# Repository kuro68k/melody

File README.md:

# melody
Melody generator for XMEGA. MIDI convert for desktop included.

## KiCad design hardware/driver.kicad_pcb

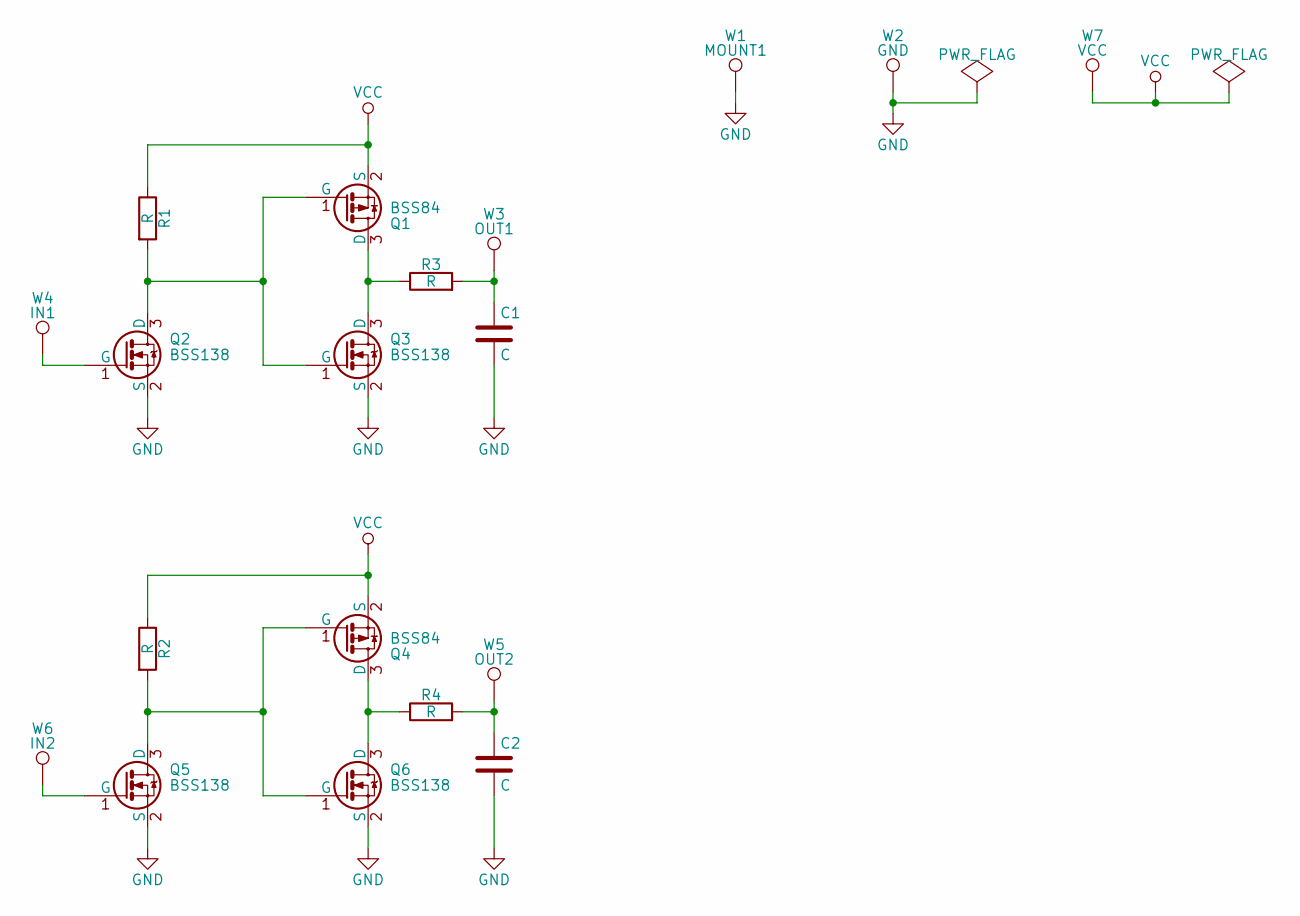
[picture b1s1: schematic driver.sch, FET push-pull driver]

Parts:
C1, C2: C; C_0603_HandSoldering
Q1, Q4: BSS84; SOT-23
Q2, Q3, Q5, Q6: BSS138; SOT-23
R1, R2, R3, R4: R; R_0603_HandSoldering
W1: MOUNT1; MountingHole_2.5mm_Pad
W2: GND; Measurement_Point_Square-TH_Big
W3: OUT1; Measurement_Point_Square-TH_Big
W4: IN1; Measurement_Point_Square-TH_Big
W5: OUT2; Measurement_Point_Square-TH_Big
W6: IN2; Measurement_Point_Square-TH_Big
W7: VCC; Measurement_Point_Square-TH_Big

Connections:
GND: C1.2, C2.2, Q2.2 (S), Q3.2 (S), Q5.2 (S), Q6.2 (S), W1.1, W2.1
unnamed: C1.1, R3.2, W3.1
unnamed: C2.1, R4.2, W5.1
unnamed: Q1.1 (G), Q2.3 (D), Q3.1 (G), R1.2
unnamed: Q1.3 (D), Q3.3 (D), R3.1
unnamed: Q2.1 (G), W4.1
unnamed: Q4.1 (G), Q5.3 (D), Q6.1 (G), R2.2
unnamed: Q4.3 (D), Q6.3 (D), R4.1
unnamed: Q5.1 (G), W6.1
VCC: Q1.2 (S), Q4.2 (S), R1.1, R2.1, W7.1

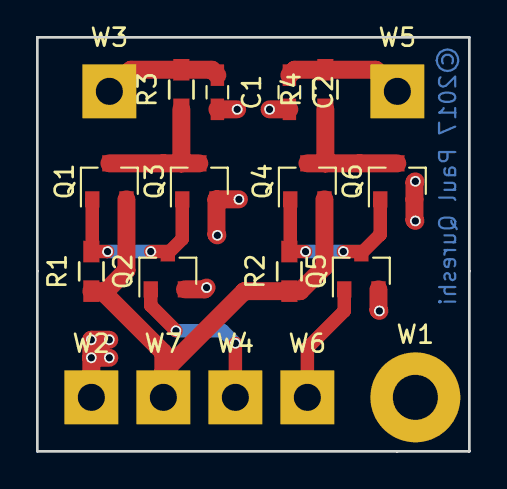
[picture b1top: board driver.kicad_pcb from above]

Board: 2 copper layers, 24.0 x 23.0 mm, 19 parts (0 on the bottom side), 10 nets.

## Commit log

2016-11-30 :confetti_ball: Added .gitattributes
2016-12-01 Added clock setup for test hardware platform
2016-12-28 Test sine wave working
2016-12-29 On-the-fly buffers working
2016-12-29 Sine wave from flash
2017-01-02 Removed some debug code
2017-01-08 Switched to test sine wave again
2017-01-08 Switched to PWM mode
2017-01-08 Fixed CPU clock
2017-01-08 128MHz PLL
2017-01-08 Enabled hi-res extension for 500KHz PWM
2017-01-08 Sine wave audible
2017-01-08 9 bit DAC
2017-01-08 PWM sample working
2017-01-08 Plays a little tune!
2017-01-13 Added control code support to midi-decode
2017-01-14 Added kamata4 tune
2017-01-15 Playback working
2017-01-15 Optimization attempt
2017-01-30 Added speaker driver schematicf
2017-02-01 Fixed FET orientation
2017-02-01 Added power flags
2017-02-01 Names/annotation
2017-02-01 Assigned footprints
2017-02-01 Initial PCB layout
2017-02-01 Routing
2017-02-02 Added optional RC filter
2017-02-03 Added logo
2017-02-03 Top silk
2017-02-03 Outlines on top silk
2017-02-05 Annotation completed
2017-02-05 PCB page notes
2017-02-05 Added licence info
2017-02-05 DRC, output
2017-02-05 Excluded V1.0 files from git
2017-02-20 Reduced mixing loop from ~750us to ~220us
2017-02-26 Test for mixer code with WAV output
2017-02-26 PWM fixed, sounds good
2017-03-11 per channel decay control for better note release
2017-07-23 debug output decoder
2017-07-23 debug output
2017-07-23 removed VS readme.txt
2017-07-23 Updated to match firmware
2017-07-23 removed debug, used stdio_fast instead
2017-07-23 Fixed decay LUT off by one error

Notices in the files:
hardware/driver.kicad_pcb:
CC BY-SA
©2017 Paul Qureshi
